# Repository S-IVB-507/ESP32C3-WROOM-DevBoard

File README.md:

# ESP32C3-WROOM-DevBoard
ESP32C3-WROOM-DevBoardの開発用ボードです。\
5列ピッチのブレッドボードでも利用できるよう、基板サイズは細くなっています。\
実機の製作及び動作確認はまだ行っていません。

# 補足事項
回路図については[ESP32C3-WROOM-02 データシート(EN)](https://www.espressif.com/sites/default/files/documentation/esp32-c3-wroom-02_datasheet_en.pdf)を参考にしています。\
GCT_USB4215-03-Aのシンボル及びフットプリントについては、[SnapMagic(SnapEDA)](https://www.snapeda.com/)より取得したものを使用しています。オリジナルデータはGCTによって作成されました。このボードではシンボル配置やパッドサイズを一部改変したうえで使用しています。\
また、上記及びLS6J2M-Tを除くその他のシンボル及びフットプリントについては、KiCADの標準ライブラリを使用しています。

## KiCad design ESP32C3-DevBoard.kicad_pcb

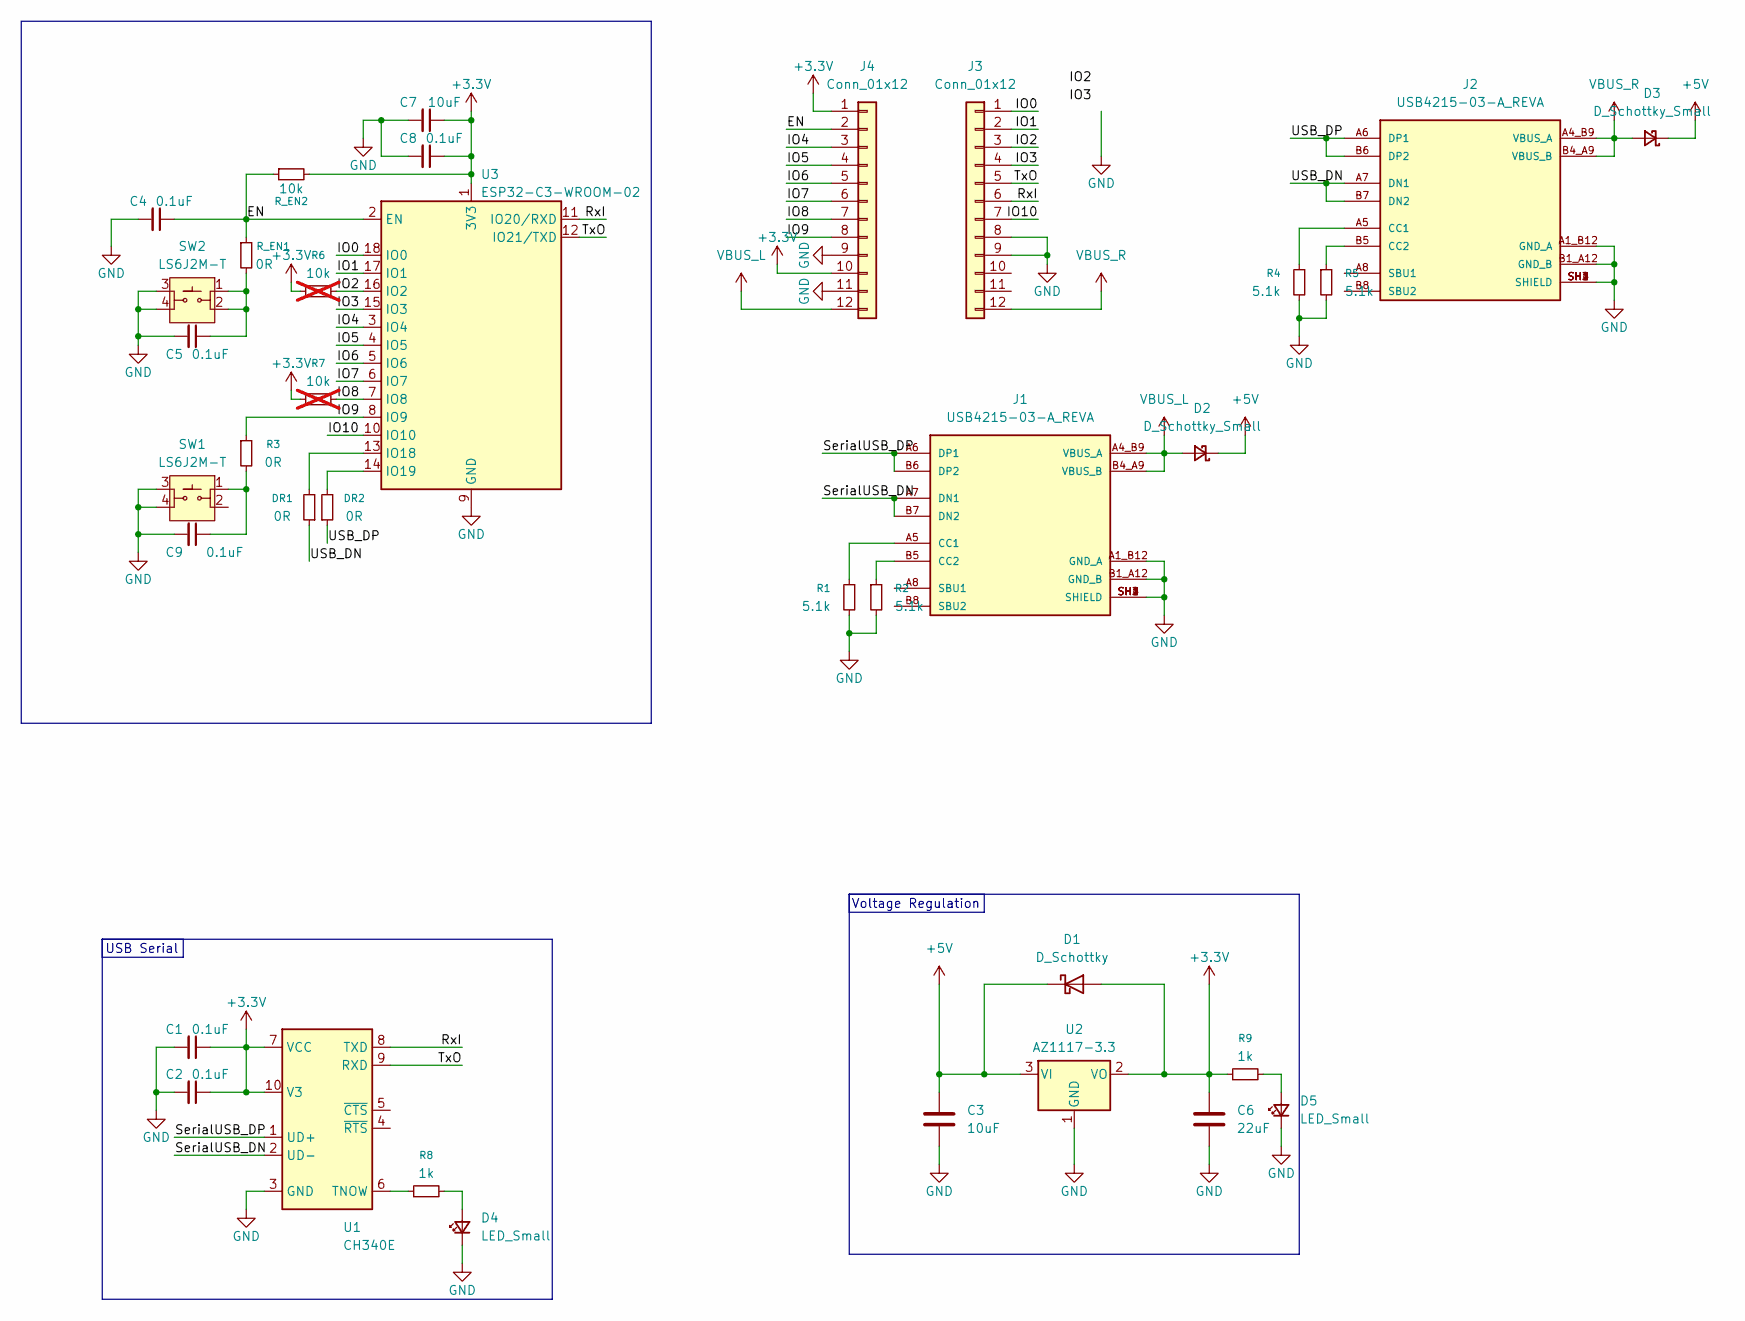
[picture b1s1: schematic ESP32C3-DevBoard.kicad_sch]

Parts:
C1, C2, C4, C5, C8, C9: 0.1uF; C_0603_1608Metric
C3, C7: 10uF; C_0603_1608Metric
C6: 22uF; C_0603_1608Metric
D1: D_Schottky; D_SOD-123
D2, D3: D_Schottky_Small; D_SOD-123
D4, D5: LED_Small; LED_0603_1608Metric
DR1, DR2: 0R; R_0402_1005Metric_Pad0.72x0.64mm_HandSolder
J1, J2: USB4215-03-A_REVA; GCT_USB4215-03-A_REVA; PARTREV A
J3, J4: Conn_01x12; PinHeader_1x12_P2.54mm_Vertical
R1, R2, R4, R5: 5.1k; R_0402_1005Metric
R3: 0R; R_0603_1608Metric
R6, R7: 10k; R_0603_1608Metric; not fitted
R8, R9: 1k; R_0603_1608Metric
R_EN1: 0R; R_0603_1608Metric
R_EN2: 10k; R_0603_1608Metric
SW1, SW2: LS6J2M-T
U1: CH340E; MSOP-10_3x3mm_P0.5mm
U2: AZ1117-3.3; SOT-223-3_TabPin2
U3: ESP32-C3-WROOM-02

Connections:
+3.3V: C1.1, C2.1, C6.1, C7.1, C8.1, D1.2 (A), J4.1, J4.10, R6.1, R7.1, R9.1, R_EN2.2, U1.7 (VCC), U1.10 (V3), U2.2 (VO), U3.1 (3V3)
+5V: C3.1, D1.1 (K), D2.1 (K), D3.1 (K), U2.3 (VI)
/EN: C4.1, J4.2, R_EN1.1, R_EN2.1, U3.2 (EN)
/IO0: J3.1, U3.18 (IO0)
/IO1: J3.2, U3.17 (IO1)
/IO2: J3.3, R6.2, U3.16 (IO2)
/IO3: J3.4, U3.15 (IO3)
/IO4: J4.3, U3.3 (IO4)
/IO5: J4.4, U3.4 (IO5)
/IO6: J4.5, U3.5 (IO6)
/IO7: J4.6, U3.6 (IO7)
/IO8: J4.7, R7.2, U3.7 (IO8)
/IO9: J4.8, R3.1, U3.8 (IO9)
/IO10: J3.7, U3.10 (IO10)
/RxI: J3.6, U1.8 (TXD), U3.11 (IO20/RXD)
/SerialUSB_DN: J1.A7 (DN1), J1.B7 (DN2), U1.2 (UD-)
/SerialUSB_DP: J1.A6 (DP1), J1.B6 (DP2), U1.1 (UD+)
/TxO: J3.5, U1.9 (RXD), U3.12 (IO21/TXD)
/USB_DN: DR1.1, J2.A7 (DN1), J2.B7 (DN2)
/USB_DP: DR2.1, J2.A6 (DP1), J2.B6 (DP2)
GND: C1.2, C2.2, C3.2, C4.2, C5.2, C6.2, C7.2, C8.2, C9.2, D4.1 (K), D5.1 (K), J1.A1_B12 (GND_A), J1.B1_A12 (GND_B), J1.SH1 (SHIELD), J1.SH2 (SHIELD), J1.SH3 (SHIELD), J1.SH4 (SHIELD), J2.A1_B12 (GND_A), J2.B1_A12 (GND_B), J2.SH1 (SHIELD), J2.SH2 (SHIELD), J2.SH3 (SHIELD), J2.SH4 (SHIELD), J3.8, J3.9, J4.9, J4.11, R1.2, R2.2, R4.2, R5.2, SW1.3, SW1.4, SW2.3, SW2.4, U1.3 (GND), U2.1 (GND), U3.9 (GND), U3.19 (GND)
unnamed: C5.1, R_EN1.2, SW2.1, SW2.2
unnamed: C9.1, R3.2, SW1.1
unnamed: D4.2 (A), R8.2
unnamed: D5.2 (A), R9.2
unnamed: J1.A5 (CC1), R1.1
unnamed: J1.B5 (CC2), R2.1
unnamed: J2.A5 (CC1), R4.1
unnamed: J2.B5 (CC2), R5.1
unnamed: R8.1, U1.6 (TNOW)
unnamed: DR1.2, U3.13 (IO18)
unnamed: DR2.2, U3.14 (IO19)
VBUS_L: D2.2 (A), J1.A4_B9 (VBUS_A), J1.B4_A9 (VBUS_B), J4.12
VBUS_R: D3.2 (A), J2.A4_B9 (VBUS_A), J2.B4_A9 (VBUS_B), J3.12

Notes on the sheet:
Voltage Regulation
USB Serial

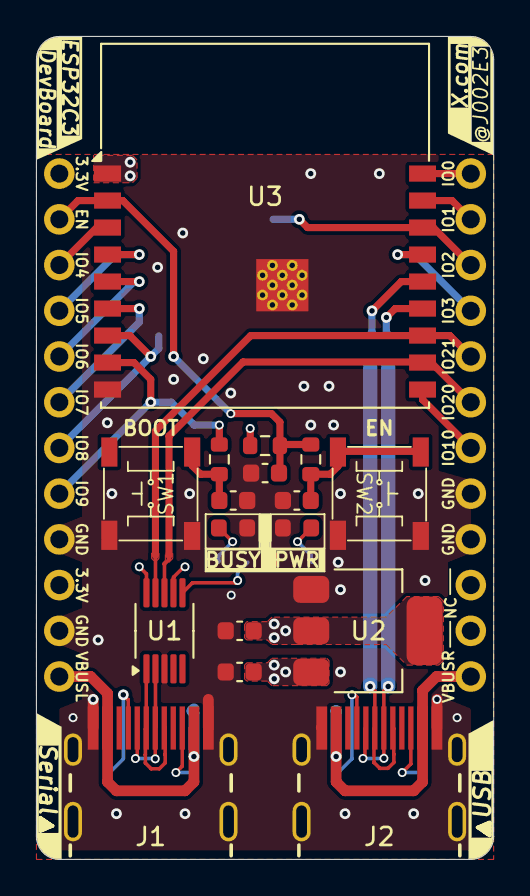
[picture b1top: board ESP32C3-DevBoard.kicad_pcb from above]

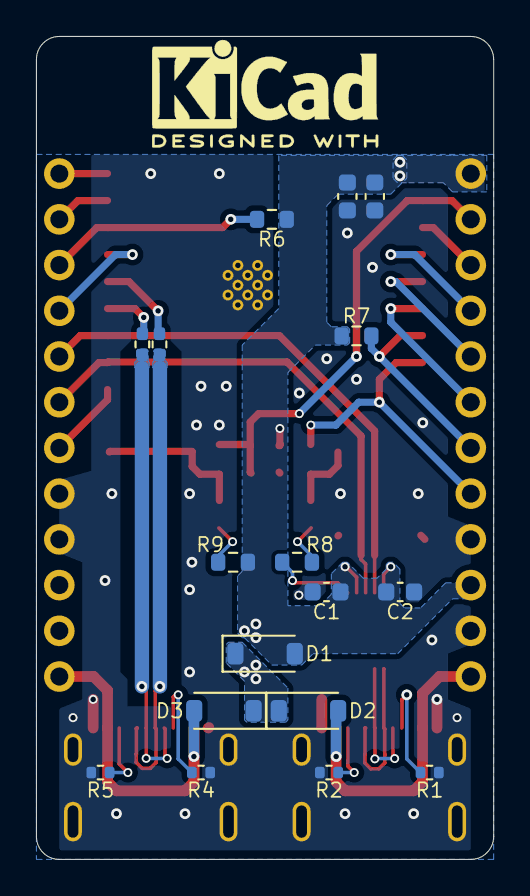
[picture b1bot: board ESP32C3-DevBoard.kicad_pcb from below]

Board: 2 copper layers, 25.4 x 45.7 mm, 36 parts (19 on the bottom side), 34 nets.

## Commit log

2025-09-06 orderd pcb layout
2025-09-06 Added README.md
